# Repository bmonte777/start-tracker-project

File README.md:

# Star Tracker Project (working name)

Open-source 3-axis motorised astro head: star tracking, go-to, panoramas, time-lapse and camera control. 3D-printed prototype first, then mass production. Built to be repaired by its owner.

## Status
- Phase 1: research — done → [`docs/01-research-report.md`](docs/01-research-report.md)
- Phase 2: engineering spec — done → [`docs/02-engineering-spec.md`](docs/02-engineering-spec.md), parts list in [`hardware/bom/master-parts-list.csv`](hardware/bom/master-parts-list.csv), calculations in [`docs/calc/`](docs/calc/), decisions D1–D32 in [`docs/02-decisions-log.md`](docs/02-decisions-log.md). The spec is at revision C: size-17 reducer (D17) and 48 mm motor (D32) on azimuth. Nothing is awaiting approval

## Repository layout (planned)
| Folder | Contents |
|---|---|
| `docs/` | Research, specs, user guide, maintenance guide |
| `hardware/cad/` | 3D models (STEP for production, STL for printing) |
| `hardware/drawings/` | A4 dimensioned drawings, one part per sheet (PDF) |
| `hardware/bom/` | Bill of materials, down to the last screw, with supplier part numbers |
| `electronics/` | Schematics and PCB (KiCad) |
| `firmware/` | Motion core + application core (ASCOM Alpaca, LX200, WebSocket) |
| `app/` | Android and Windows apps |
| `website/` | Product website |

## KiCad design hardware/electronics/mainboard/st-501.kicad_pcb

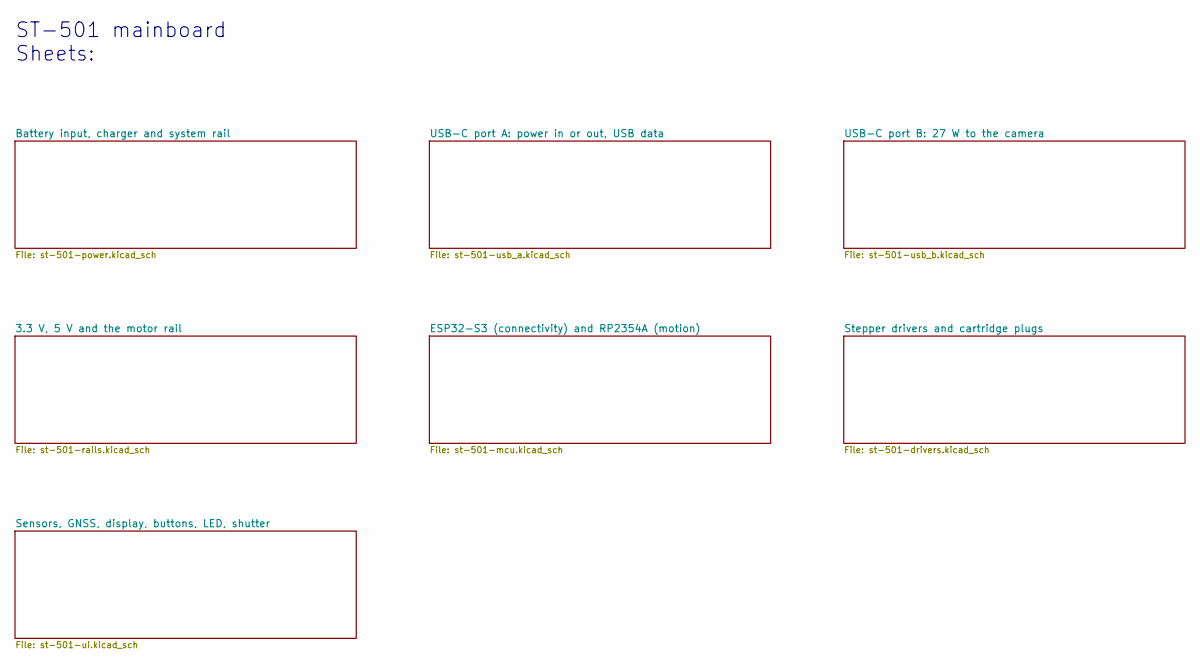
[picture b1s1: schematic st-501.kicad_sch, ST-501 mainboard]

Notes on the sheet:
ST-501 mainboard Sheets:

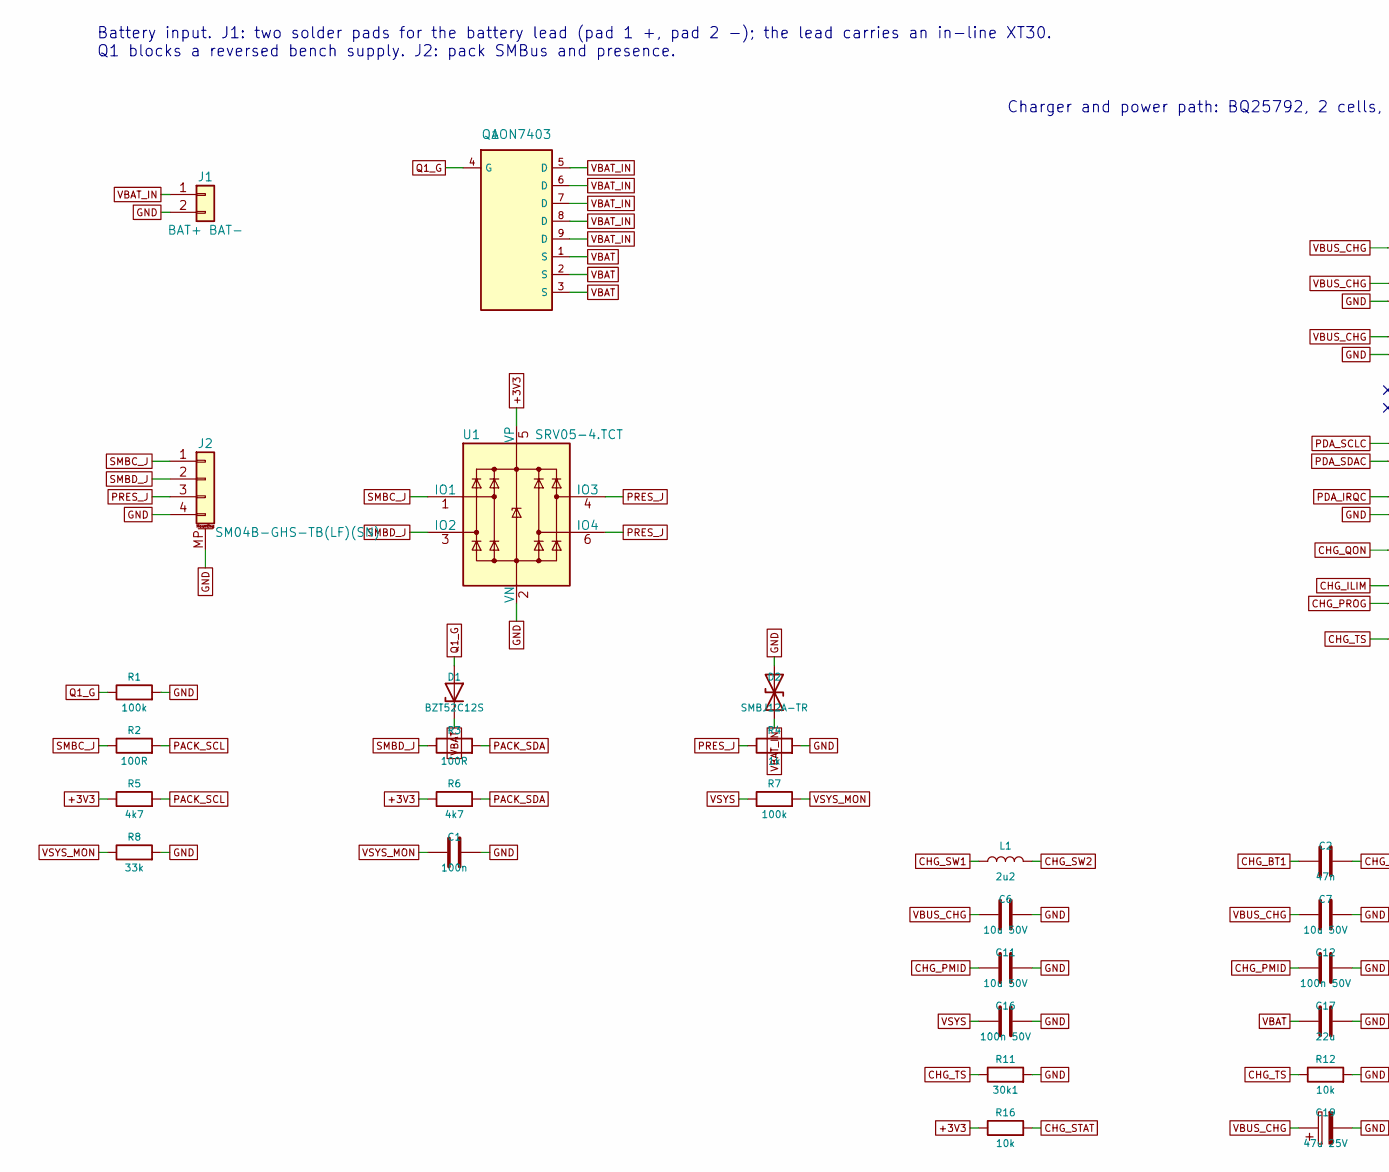
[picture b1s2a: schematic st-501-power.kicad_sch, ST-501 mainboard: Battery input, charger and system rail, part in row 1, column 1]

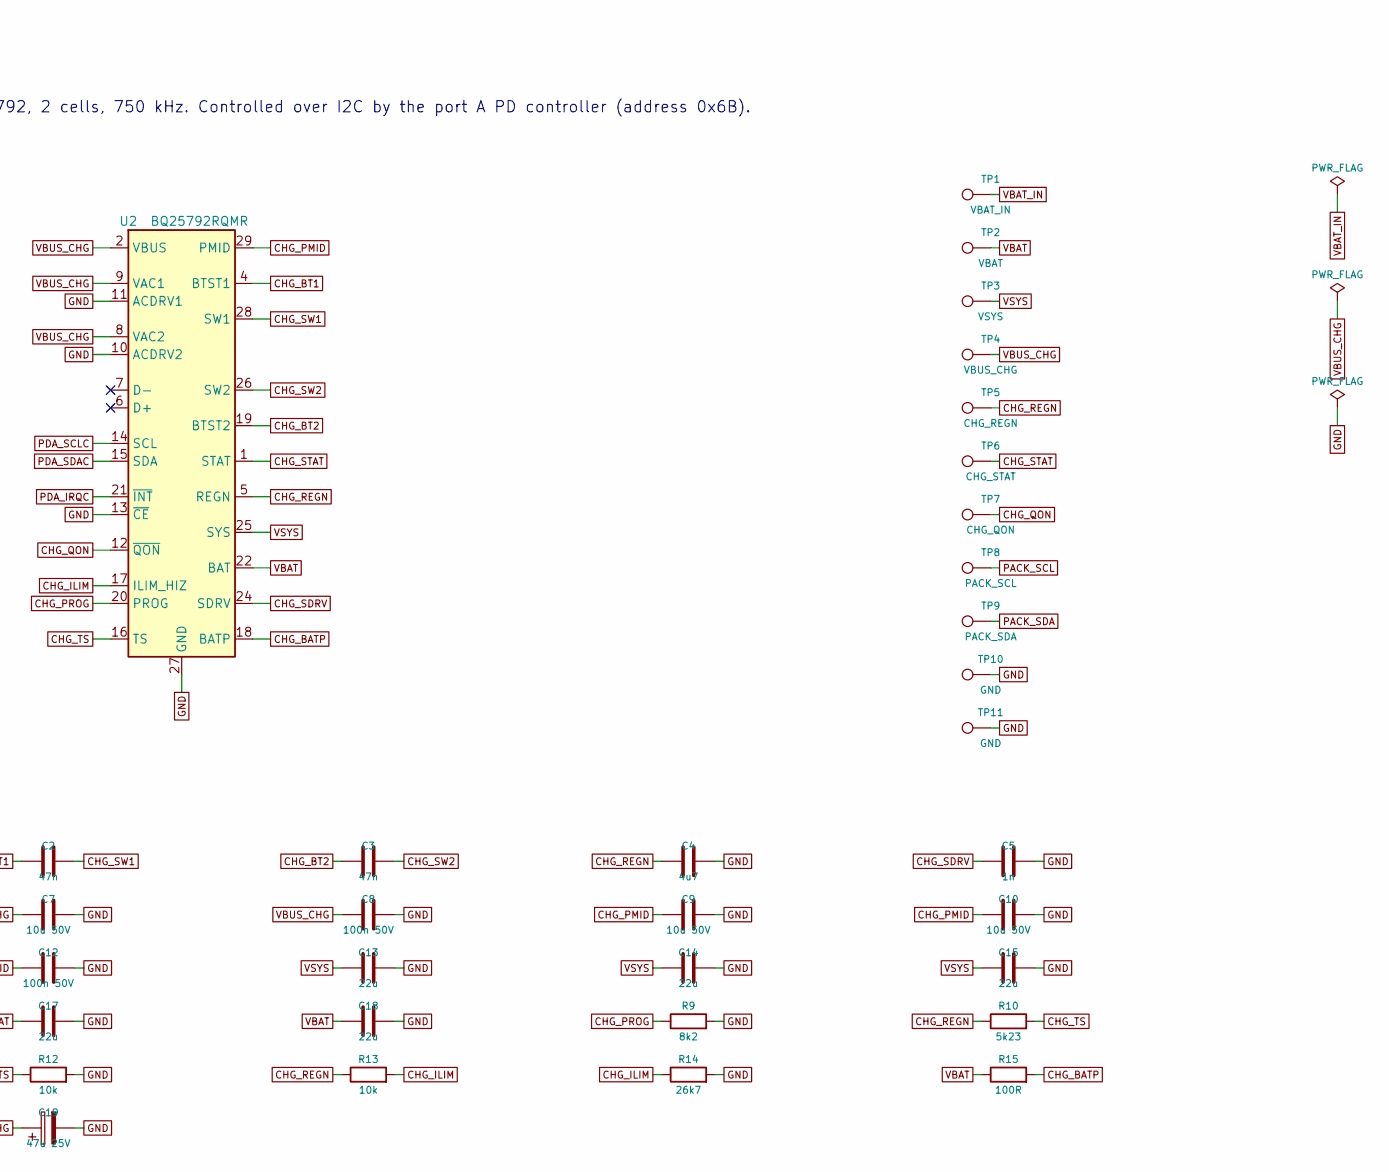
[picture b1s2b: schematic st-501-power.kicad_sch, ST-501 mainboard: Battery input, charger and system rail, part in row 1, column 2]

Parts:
C1: 100n; C_0402_1005Metric; MPN CL05B104KO5NNNC; LCSC C1525
C2, C3: 47n; C_0402_1005Metric; MPN 47 nF X7R 25 V 0402
C4: 4u7; C_0603_1608Metric; MPN CL10A475KO8NNNC; LCSC C19666
C5: 1n; C_0402_1005Metric; MPN 0402B102K500NT; LCSC C1523
C6, C7, C9, C10, C11: 10u 50V; C_1206_3216Metric; MPN CL31A106KBHNNNE; LCSC C13585
C8, C12, C16: 100n 50V; C_0402_1005Metric; MPN CL05B104KB54PNC; LCSC C307331
C13, C14, C15, C17, C18: 22u; C_0805_2012Metric; MPN CL21A226MAQNNNE; LCSC C45783
C19: 47u 25V; CP_Elec_6.3x5.8; MPN 47 uF 25 V polymer
D1: BZT52C12S; D_SOD-323; MPN BZT52C12S; LCSC C14643
D2: SMBJ12A-TR; D_SMB; MPN SMBJ12A-TR; LCSC C133677
J1: BAT+ BAT-; WirePads_1x02_P5.0mm_3.5x5mm
J2: SM04B-GHS-TB(LF)(SN); JST_GH_SM04B-GHS-TB_1x04-1MP_P1.25mm_Horizontal; MPN SM04B-GHS-TB(LF)(SN); LCSC C189895
L1: 2u2; L_Sunlord_MWSA0603S; MPN MWSC0630H2R2MT
Q1: AON7403; DFN-8-1EP_3x3mm_P0.65mm_EP1.55x2.4mm; MPN AON7403; LCSC C5310961
R1, R7: 100k; R_0402_1005Metric; MPN 0402WGF1003TCE; LCSC C25741
R2, R3, R15: 100R; R_0402_1005Metric; MPN 0402WGF1000TCE; LCSC C25076
R4: 1k; R_0402_1005Metric; MPN 0402WGF1001TCE; LCSC C11702
R5, R6: 4k7; R_0402_1005Metric; MPN 0402WGF4701TCE; LCSC C25900
R8: 33k; R_0402_1005Metric; MPN 0402WGF3302TCE; LCSC C25779
R9: 8k2; R_0402_1005Metric; MPN 0402WGF8201TCE; LCSC C25924
R10: 5k23; R_0402_1005Metric; MPN RC0402FR-075K23L; LCSC C477746
R11: 30k1; R_0402_1005Metric; MPN RC0402FR-0730K1L; LCSC C138009
R12, R13, R16: 10k; R_0402_1005Metric; MPN 0402WGF1002TCE; LCSC C25744
R14: 26k7; R_0402_1005Metric; MPN RC0402FR-0726K7L
TP1: VBAT_IN; TestPoint_Pad_D1.0mm
TP2: VBAT; TestPoint_Pad_D1.0mm
TP3: VSYS; TestPoint_Pad_D1.0mm
TP4: VBUS_CHG; TestPoint_Pad_D1.0mm
TP5: CHG_REGN; TestPoint_Pad_D1.0mm
TP6: CHG_STAT; TestPoint_Pad_D1.0mm
TP7: CHG_QON; TestPoint_Pad_D1.0mm
TP8: PACK_SCL; TestPoint_Pad_D1.0mm
TP9: PACK_SDA; TestPoint_Pad_D1.0mm
TP10, TP11: GND; TestPoint_Pad_D1.0mm
U1: SRV05-4.TCT; SOT-23-6; MPN SRV05-4.TCT; LCSC C2687126
U2: BQ25792RQMR; Texas_RQM0029A_VQFN-29_4x4mm_P0.4mm; MPN BQ25792RQMR; LCSC C2862876

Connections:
+3V3: R5.1, R6.1, R16.1, U1.5 (VP); also elsewhere on the board
CHG_BATP: R15.2, U2.18 (BATP)
CHG_BT1: C2.1, U2.4 (BTST1)
CHG_BT2: C3.1, U2.19 (BTST2)
CHG_ILIM: R13.2, R14.1, U2.17 (ILIM_HIZ)
CHG_PMID: C9.1, C10.1, C11.1, C12.1, U2.29 (PMID)
CHG_PROG: R9.1, U2.20 (PROG)
CHG_QON: TP7.1, U2.12 (~QON)
CHG_REGN: C4.1, R10.1, R13.1, TP5.1, U2.5 (REGN)
CHG_SDRV: C5.1, U2.24 (SDRV)
CHG_STAT: R16.2, TP6.1, U2.1 (STAT)
CHG_SW1: C2.2, L1.1, U2.28 (SW1)
CHG_SW2: C3.2, L1.2, U2.26 (SW2)
CHG_TS: R10.2, R11.1, R12.1, U2.16 (TS)
GND: C1.2, C4.2, C5.2, C6.2, C7.2, C8.2, C9.2, C10.2, C11.2, C12.2, C13.2, C14.2, C15.2, C16.2, C17.2, C18.2, C19.2, D2.2 (A2), J1.2, J2.4, J2.MP (MountPin), R1.2, R4.2, R8.2, R9.2, R11.2, R12.2, R14.2, TP10.1, TP11.1, U1.2 (VN), U2.10 (ACDRV2), U2.11 (ACDRV1), U2.13 (~CE), U2.27 (GND); also elsewhere on the board
PACK_SCL: R2.2, R5.2, TP8.1; also elsewhere on the board
PACK_SDA: R3.2, R6.2, TP9.1; also elsewhere on the board
PDA_IRQC: U2.21 (~INT); also elsewhere on the board
PDA_SCLC: U2.14 (SCL); also elsewhere on the board
PDA_SDAC: U2.15 (SDA); also elsewhere on the board
PRES_J: J2.3, R4.1, U1.4 (IO3), U1.6 (IO4)
Q1_G: D1.2 (A), Q1.4 (G), R1.1
SMBC_J: J2.1, R2.1, U1.1 (IO1)
SMBD_J: J2.2, R3.1, U1.3 (IO2)
VBAT: C17.1, C18.1, D1.1 (K), Q1.1 (S), Q1.2 (S), Q1.3 (S), R15.1, TP2.1, U2.22 (BAT), U2.23 (BAT)
VBAT_IN: D2.1 (A1), J1.1, Q1.5 (D), Q1.6 (D), Q1.7 (D), Q1.8 (D), Q1.9 (D), TP1.1
VBUS_CHG: C6.1, C7.1, C8.1, C19.1, TP4.1, U2.2 (VBUS), U2.3 (VBUS), U2.8 (VAC2), U2.9 (VAC1); also elsewhere on the board
VSYS: C13.1, C14.1, C15.1, C16.1, R7.1, TP3.1, U2.25 (SYS); also elsewhere on the board
VSYS_MON: C1.1, R7.2, R8.1; also elsewhere on the board

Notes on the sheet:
Battery input. J1: two solder pads for the battery lead (pad 1 +, pad 2 -); the lead carries an in-line XT30. Q1 blocks a reversed bench supply. J2: pack SMBus and presence.
Charger and power path: BQ25792, 2 cells, 750 kHz. Controlled over I2C by the port A PD controller (address 0x6B).

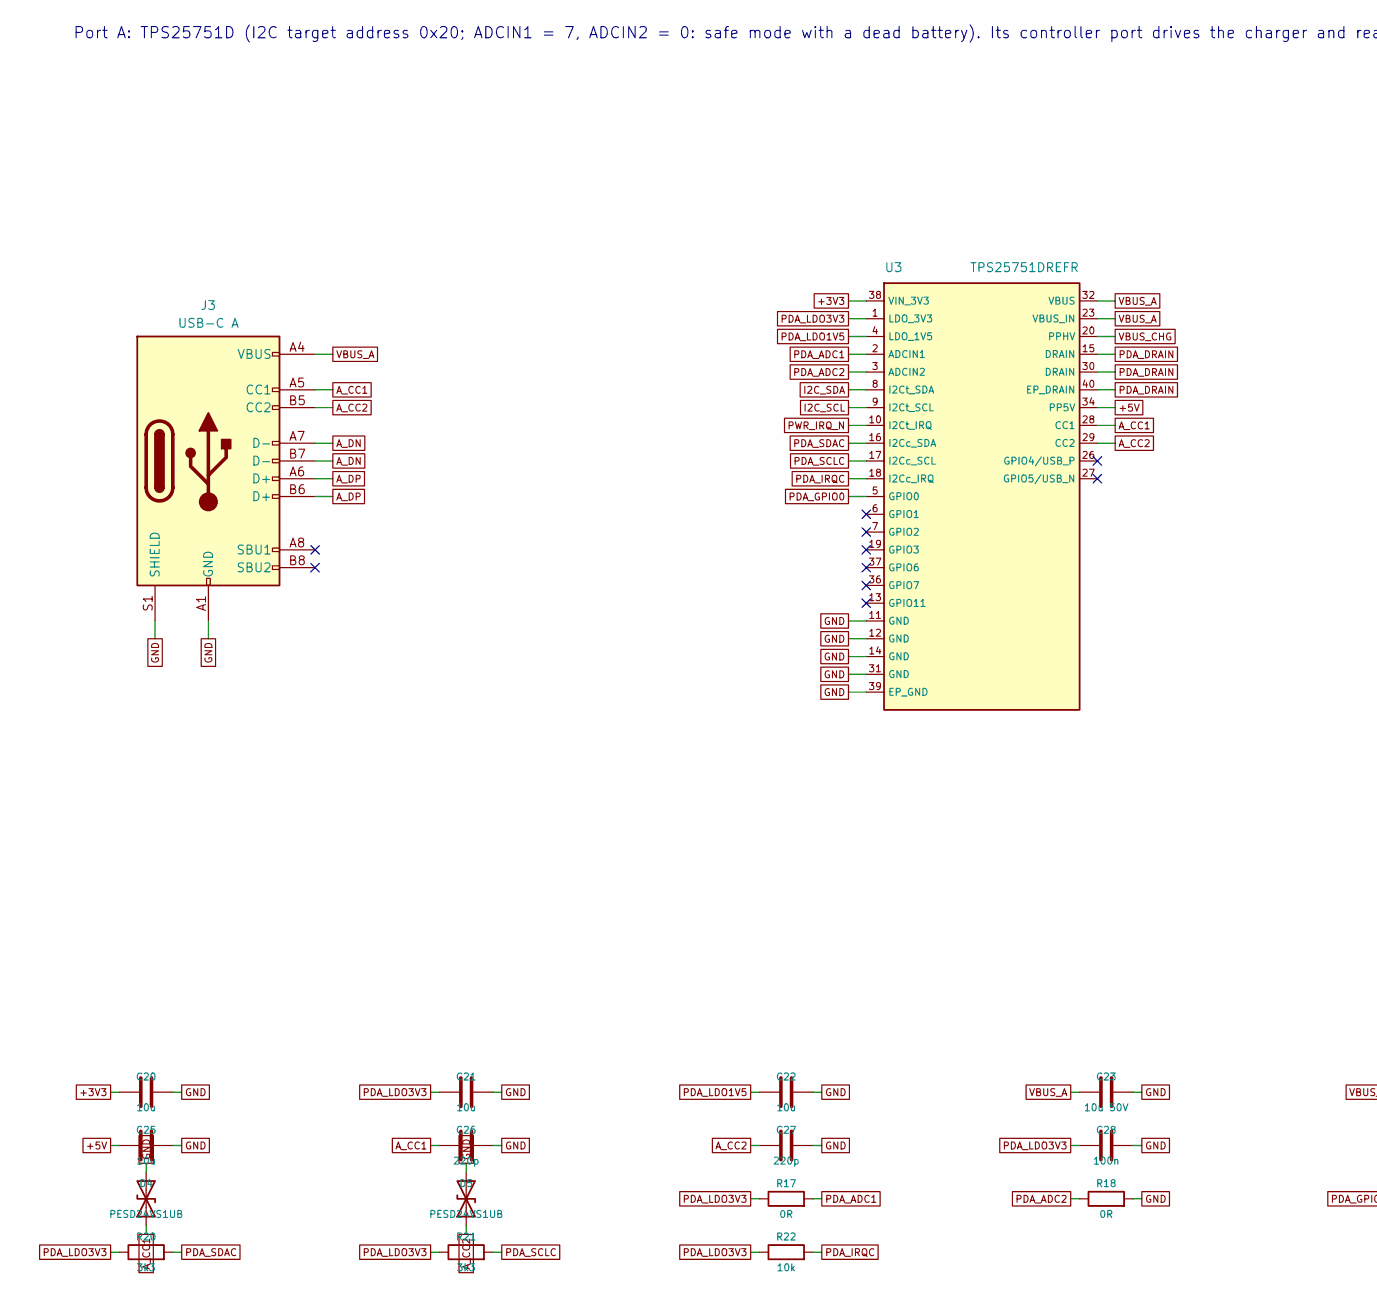
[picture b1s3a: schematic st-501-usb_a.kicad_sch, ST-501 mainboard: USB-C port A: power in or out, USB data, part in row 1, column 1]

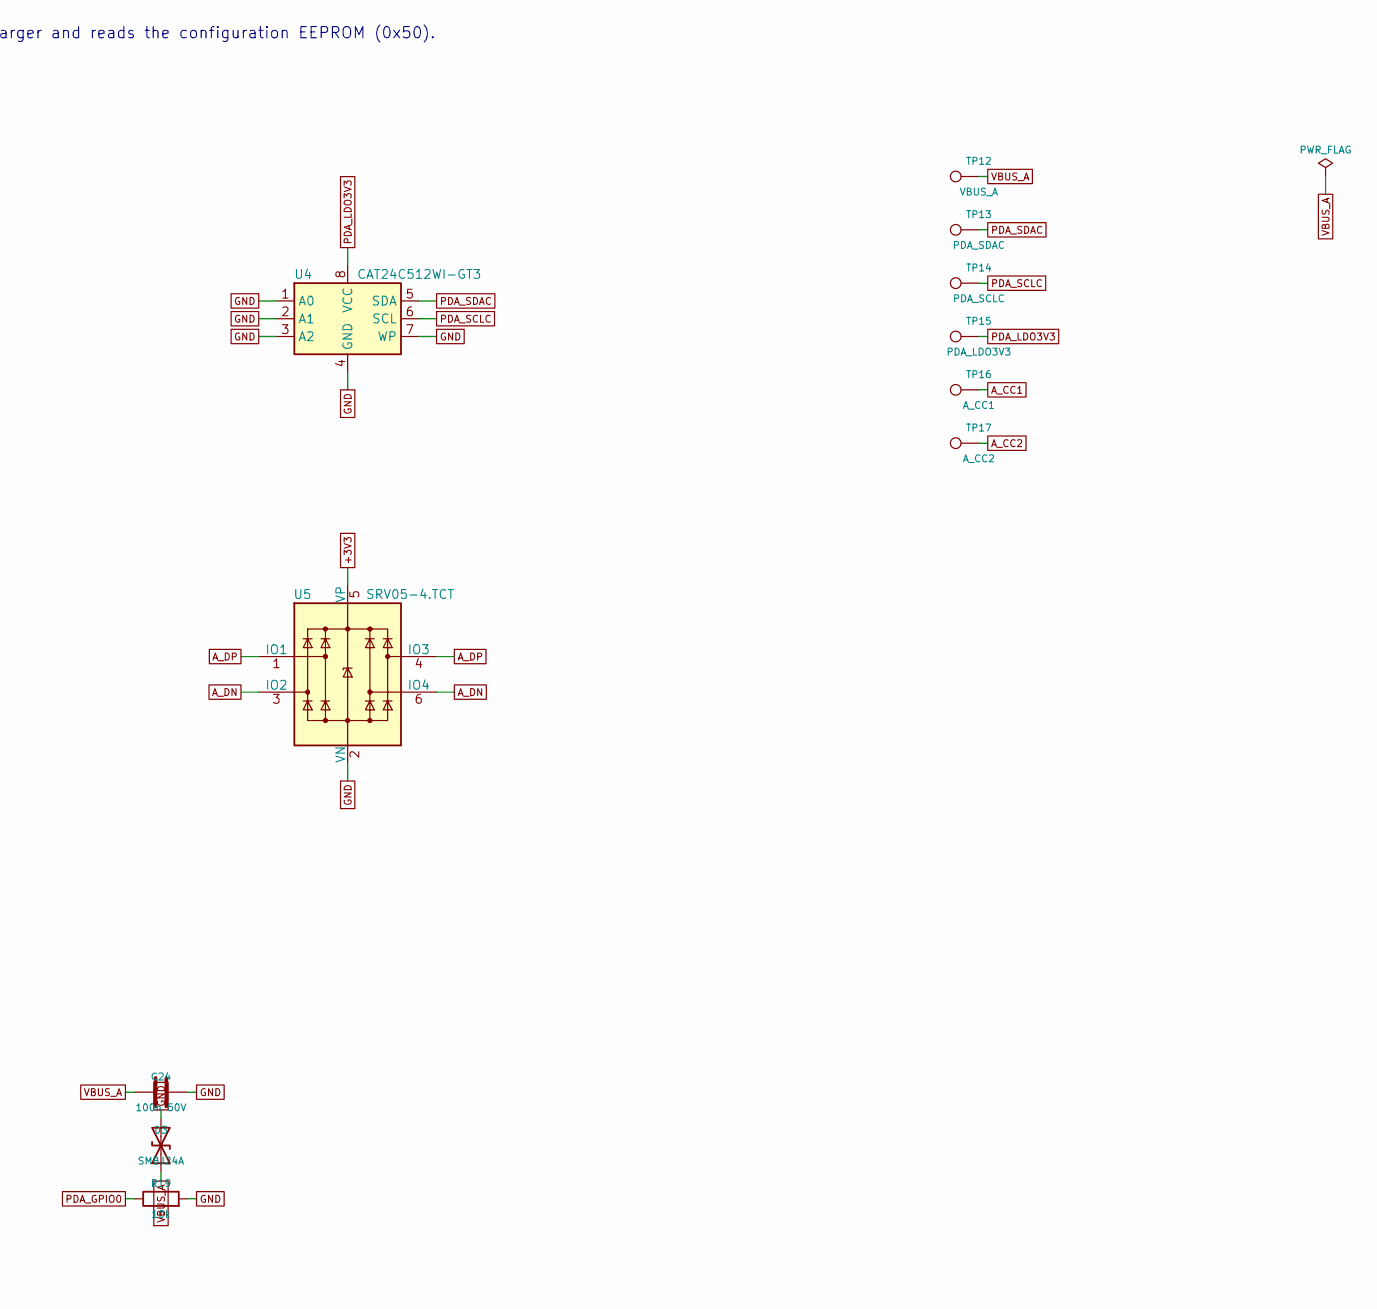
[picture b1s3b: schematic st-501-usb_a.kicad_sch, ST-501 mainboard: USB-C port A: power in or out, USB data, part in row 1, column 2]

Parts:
C20, C21, C22, C25: 10u; C_0603_1608Metric; MPN CL10A106KP8NNNC; LCSC C19702
C23: 10u 50V; C_1206_3216Metric; MPN CL31A106KBHNNNE; LCSC C13585
C24: 100n 50V; C_0402_1005Metric; MPN CL05B104KB54PNC; LCSC C307331
C26, C27: 220p; C_0402_1005Metric; MPN 0402B221K500NT; LCSC C1530
C28: 100n; C_0402_1005Metric; MPN CL05B104KO5NNNC; LCSC C1525
D3: SMBJ24A; D_SMB; MPN SMBJ24A; LCSC C353373
D4, D5: PESD24VS1UB; D_SOD-323; MPN PESD24VS1UB
J3: USB-C A; USB_C_Receptacle_G-Switch_GT-USB-7051x; MPN GT-USB-7051A; LCSC C2843970
R17, R18: 0R; R_0402_1005Metric; MPN 0402WGF0000TCE; LCSC C17168
R19, R22: 10k; R_0402_1005Metric; MPN 0402WGF1002TCE; LCSC C25744
R20, R21: 3k3; R_0402_1005Metric; MPN 0402WGF3301TCE; LCSC C25890
TP12: VBUS_A; TestPoint_Pad_D1.0mm
TP13: PDA_SDAC; TestPoint_Pad_D1.0mm
TP14: PDA_SCLC; TestPoint_Pad_D1.0mm
TP15: PDA_LDO3V3; TestPoint_Pad_D1.0mm
TP16: A_CC1; TestPoint_Pad_D1.0mm
TP17: A_CC2; TestPoint_Pad_D1.0mm
U3: TPS25751DREFR; Texas_REF0038A_WQFN-38-2EP_6x4mm_P0.4; MPN TPS25751DREFR
U4: CAT24C512WI-GT3; SOIC-8_3.9x4.9mm_P1.27mm; MPN CAT24C512WI-GT3; LCSC C79986
U5: SRV05-4.TCT; SOT-23-6; MPN SRV05-4.TCT; LCSC C2687126

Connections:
+3V3: C20.1, U3.38 (VIN_3V3), U5.5 (VP); also elsewhere on the board
+5V: C25.1, U3.34 (PP5V); also elsewhere on the board
A_CC1: C26.1, D4.1 (A1), J3.A5 (CC1), TP16.1, U3.28 (CC1)
A_CC2: C27.1, D5.1 (A1), J3.B5 (CC2), TP17.1, U3.29 (CC2)
A_DN: J3.A7 (D-), J3.B7 (D-), U5.3 (IO2), U5.6 (IO4); also elsewhere on the board
A_DP: J3.A6 (D+), J3.B6 (D+), U5.1 (IO1), U5.4 (IO3); also elsewhere on the board
GND: C20.2, C21.2, C22.2, C23.2, C24.2, C25.2, C26.2, C27.2, C28.2, D3.2 (A2), D4.2 (A2), D5.2 (A2), J3.A1 (GND), J3.A12 (GND), J3.B1 (GND), J3.B12 (GND), J3.S1 (SHIELD), R18.2, R19.2, U3.11 (GND), U3.12 (GND), U3.14 (GND), U3.31 (GND), U3.39 (EP_GND), U4.1 (A0), U4.2 (A1), U4.3 (A2), U4.4 (GND), U4.7 (WP), U5.2 (VN); also elsewhere on the board
I2C_SCL: U3.9 (I2Ct_SCL); also elsewhere on the board
I2C_SDA: U3.8 (I2Ct_SDA); also elsewhere on the board
PDA_ADC1: R17.2, U3.2 (ADCIN1)
PDA_ADC2: R18.1, U3.3 (ADCIN2)
PDA_DRAIN: U3.15 (DRAIN), U3.30 (DRAIN), U3.40 (EP_DRAIN)
PDA_GPIO0: R19.1, U3.5 (GPIO0)
PDA_IRQC: R22.2, U3.18 (I2Cc_IRQ); also elsewhere on the board
PDA_LDO1V5: C22.1, U3.4 (LDO_1V5)
PDA_LDO3V3: C21.1, C28.1, R17.1, R20.1, R21.1, R22.1, TP15.1, U3.1 (LDO_3V3), U4.8 (VCC)
PDA_SCLC: R21.2, TP14.1, U3.17 (I2Cc_SCL), U4.6 (SCL); also elsewhere on the board
PDA_SDAC: R20.2, TP13.1, U3.16 (I2Cc_SDA), U4.5 (SDA); also elsewhere on the board
PWR_IRQ_N: U3.10 (I2Ct_IRQ); also elsewhere on the board
VBUS_A: C23.1, C24.1, D3.1 (A1), J3.A4 (VBUS), J3.A9 (VBUS), J3.B4 (VBUS), J3.B9 (VBUS), TP12.1, U3.23 (VBUS_IN), U3.32 (VBUS)
VBUS_CHG: U3.20 (PPHV); also elsewhere on the board

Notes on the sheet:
Port A: TPS25751D (I2C target address 0x20; ADCIN1 = 7, ADCIN2 = 0: safe mode with a dead battery). Its controller port drives the charger and reads the configuration EEPROM (0x50).

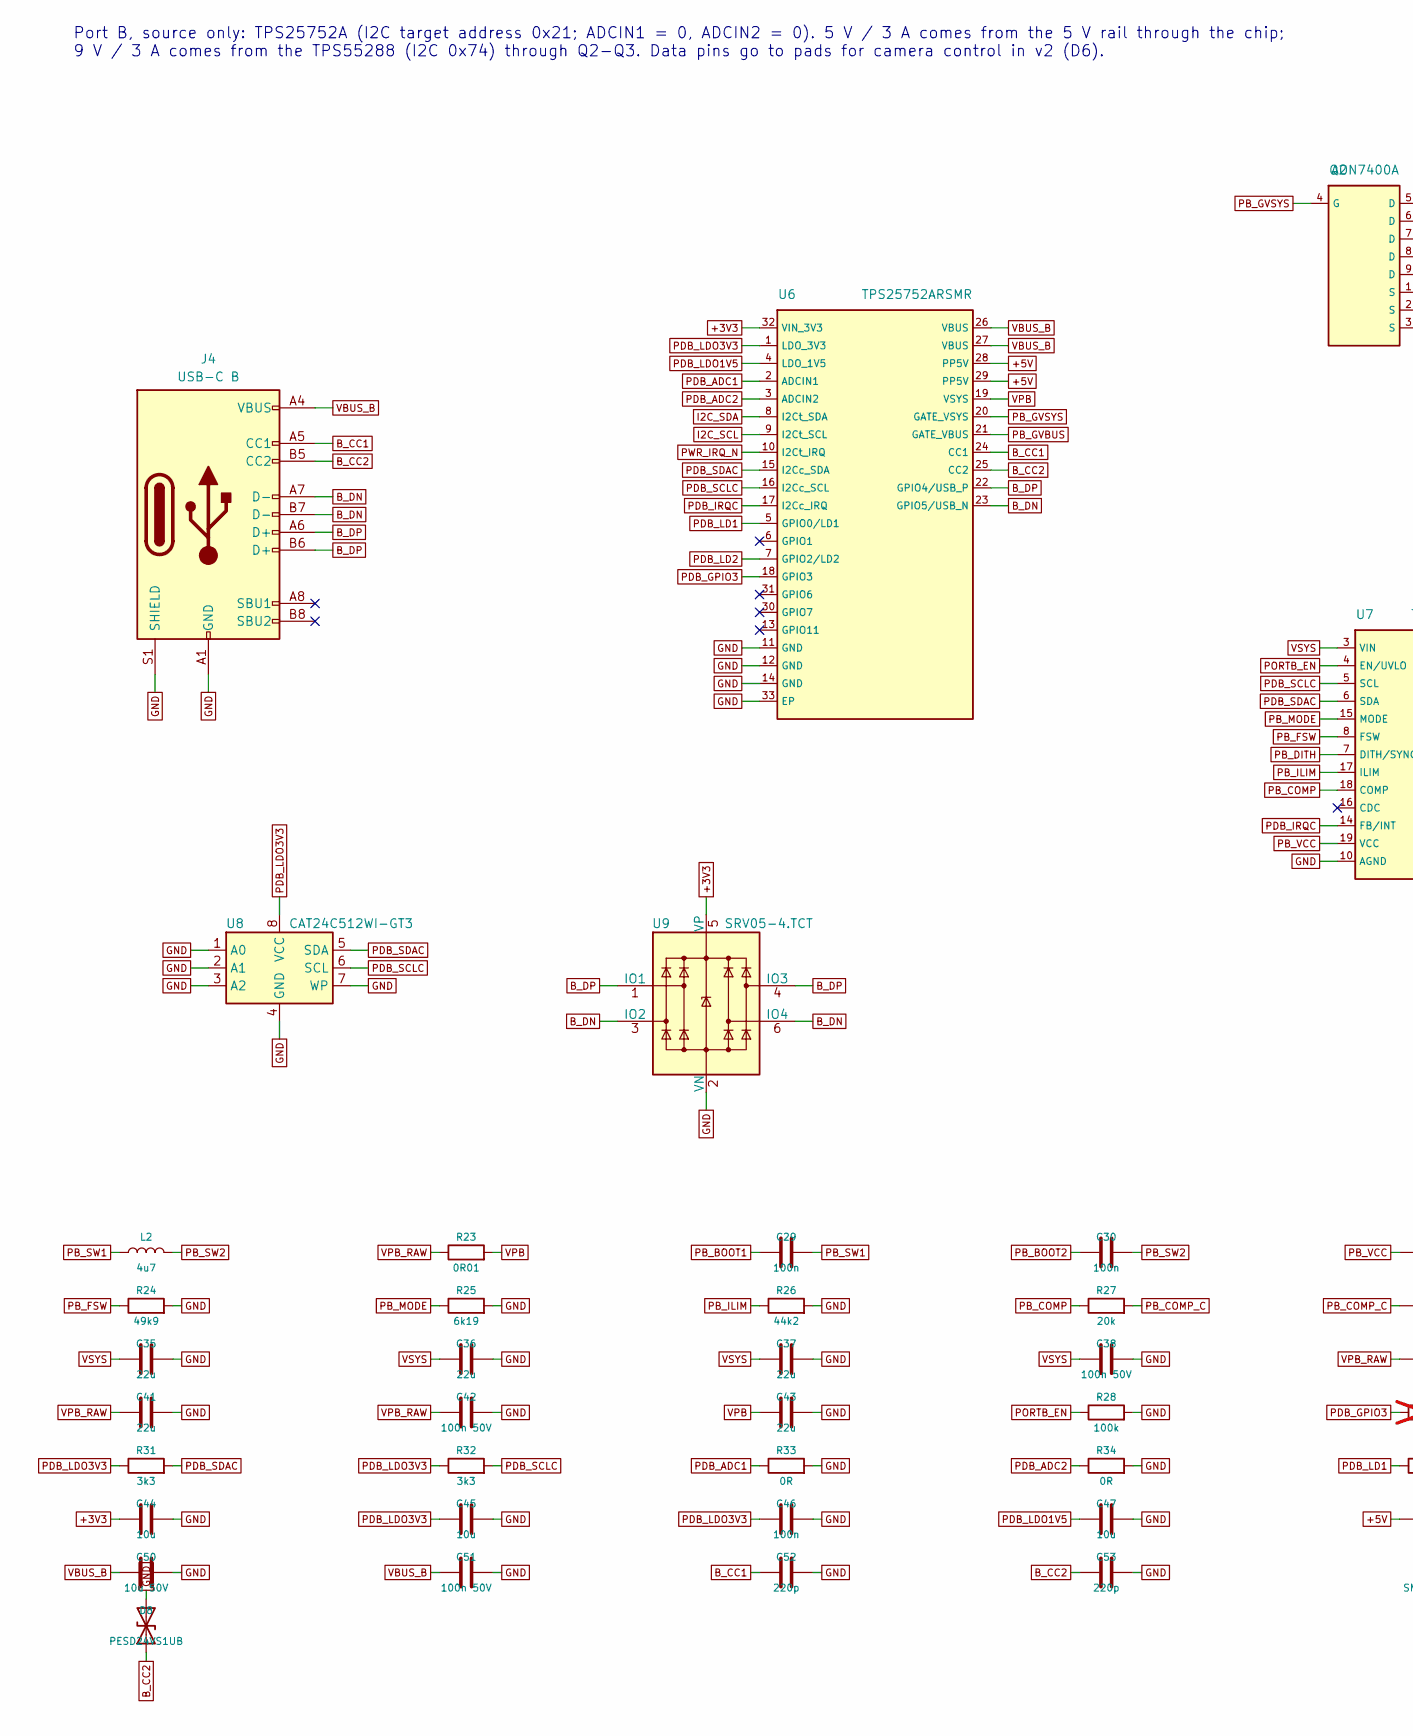
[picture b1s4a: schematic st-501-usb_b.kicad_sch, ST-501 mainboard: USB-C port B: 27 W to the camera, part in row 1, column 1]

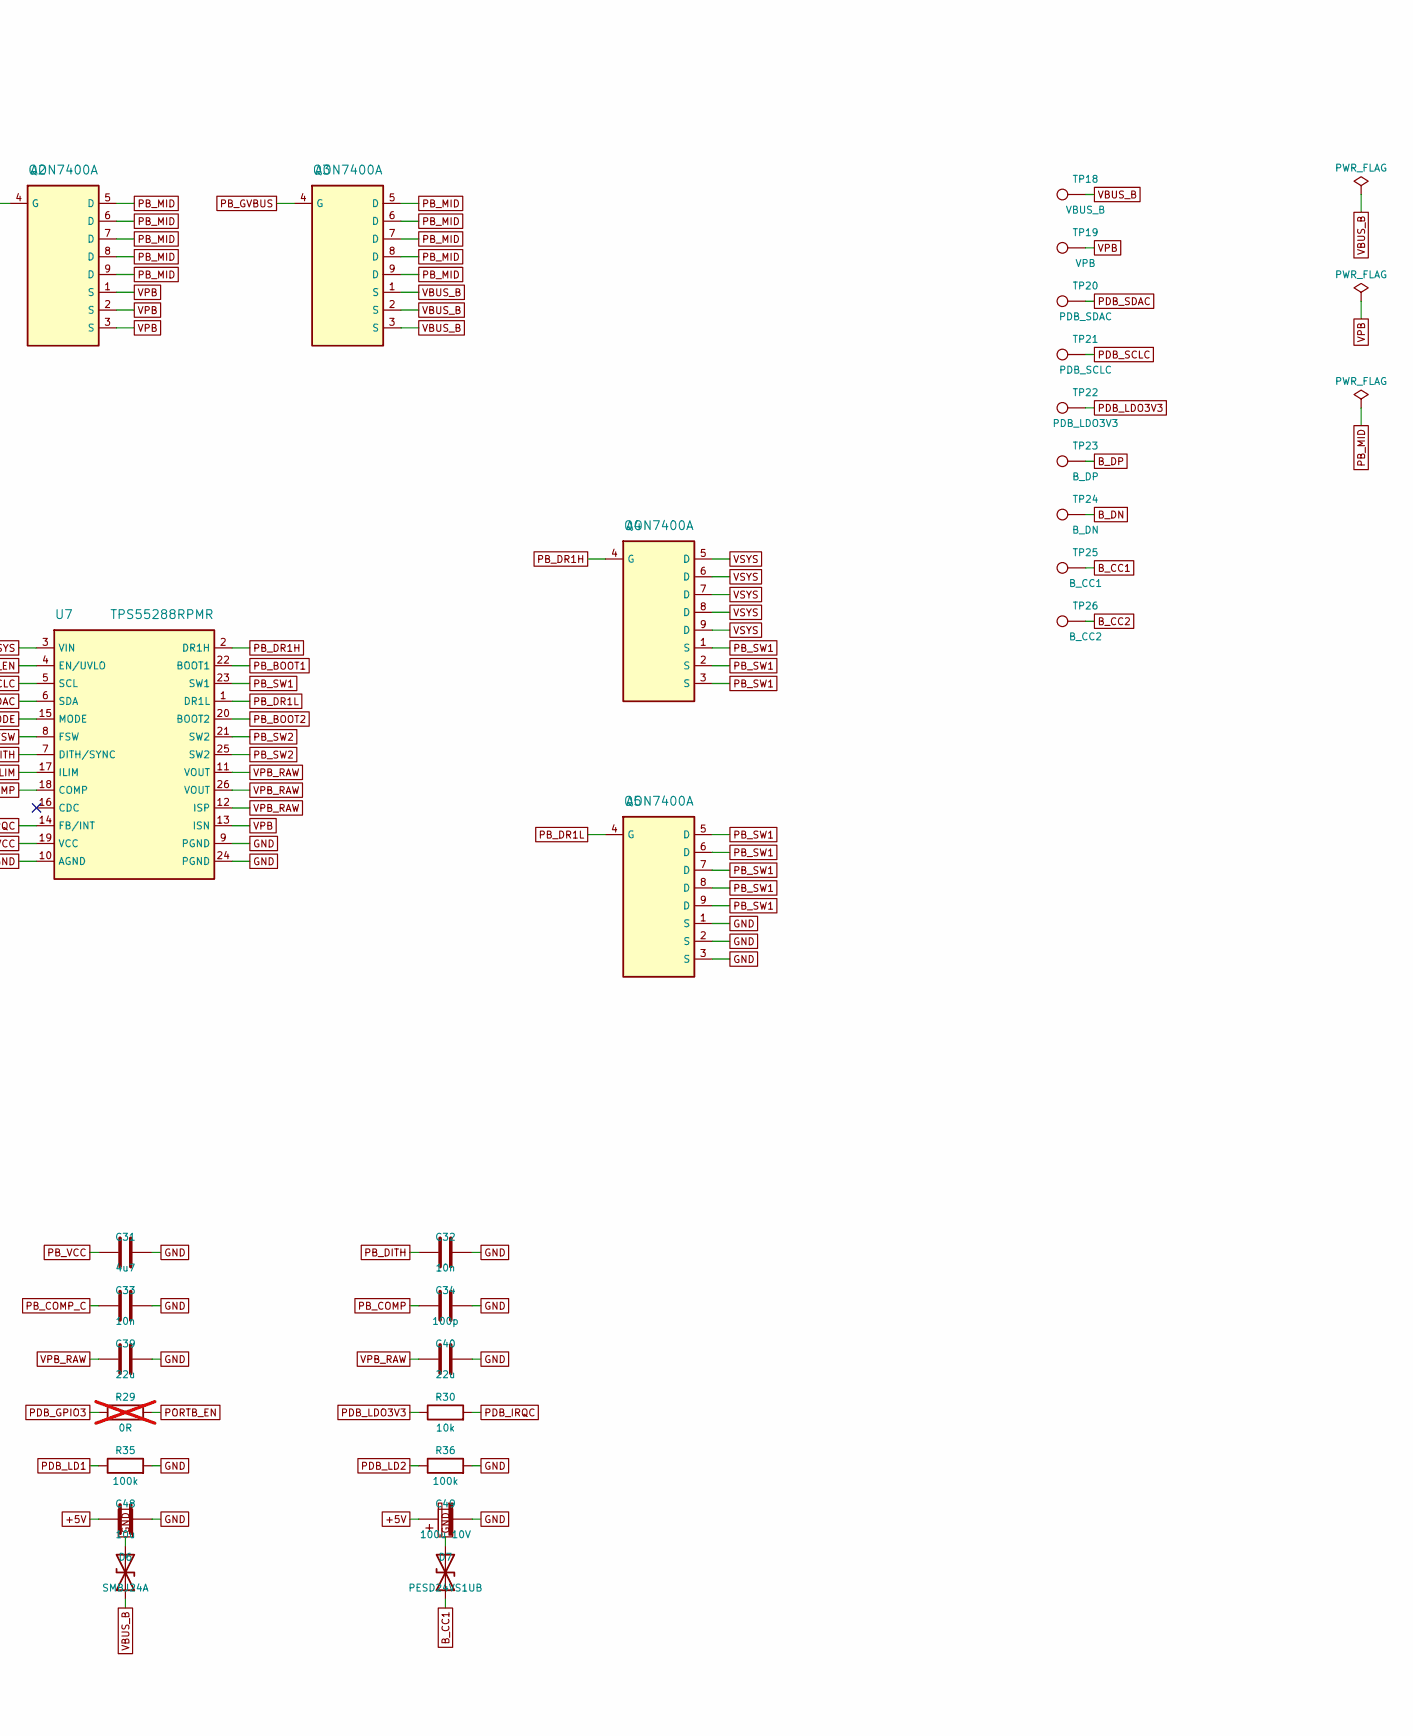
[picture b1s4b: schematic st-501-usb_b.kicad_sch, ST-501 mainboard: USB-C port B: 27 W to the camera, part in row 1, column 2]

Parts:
C29, C30, C46: 100n; C_0402_1005Metric; MPN CL05B104KO5NNNC; LCSC C1525
C31: 4u7; C_0603_1608Metric; MPN CL10A475KO8NNNC; LCSC C19666
C32, C33: 10n; C_0402_1005Metric; MPN CL05B103KB5NNNC; LCSC C15195
C34: 100p; C_0402_1005Metric; MPN CL05C101JB5NNNC; LCSC C1546
C35, C36, C37, C39, C40, C41, C43: 22u; C_0805_2012Metric; MPN CL21A226MAQNNNE; LCSC C45783
C38, C42, C51: 100n 50V; C_0402_1005Metric; MPN CL05B104KB54PNC; LCSC C307331
C44, C45, C47, C48: 10u; C_0603_1608Metric; MPN CL10A106KP8NNNC; LCSC C19702
C49: 100u 10V; CP_Elec_6.3x5.8; MPN 100 uF 10 V polymer
C50: 10u 50V; C_1206_3216Metric; MPN CL31A106KBHNNNE; LCSC C13585
C52, C53: 220p; C_0402_1005Metric; MPN 0402B221K500NT; LCSC C1530
D6: SMBJ24A; D_SMB; MPN SMBJ24A; LCSC C353373
D7, D8: PESD24VS1UB; D_SOD-323; MPN PESD24VS1UB
J4: USB-C B; USB_C_Receptacle_G-Switch_GT-USB-7051x; MPN GT-USB-7051A; LCSC C2843970
L2: 4u7; L_Sunlord_MWSA0603S; MPN MWSC0630H4R7MT; LCSC C2991788
Q2, Q3, Q4, Q5: AON7400A; DFN-8-1EP_3x3mm_P0.65mm_EP1.55x2.4mm; MPN AON7400A; LCSC C85734
R23: 0R01; R_1206_3216Metric; MPN 0.010 ohm 1 % 1 W current sense
R24: 49k9; R_0402_1005Metric; MPN 0402WGF4992TCE; LCSC C25897
R25: 6k19; R_0402_1005Metric; MPN RC0402FR-076K19L
R26: 44k2; R_0402_1005Metric; MPN RC0402FR-0744K2L
R27: 20k; R_0402_1005Metric; MPN 0402WGF2002TCE; LCSC C25765
R28, R35, R36: 100k; R_0402_1005Metric; MPN 0402WGF1003TCE; LCSC C25741
R29: 0R; R_0402_1005Metric; MPN 0402WGF0000TCE; LCSC C17168; not fitted
R30: 10k; R_0402_1005Metric; MPN 0402WGF1002TCE; LCSC C25744
R31, R32: 3k3; R_0402_1005Metric; MPN 0402WGF3301TCE; LCSC C25890
R33, R34: 0R; R_0402_1005Metric; MPN 0402WGF0000TCE; LCSC C17168
TP18: VBUS_B; TestPoint_Pad_D1.0mm
TP19: VPB; TestPoint_Pad_D1.0mm
TP20: PDB_SDAC; TestPoint_Pad_D1.0mm
TP21: PDB_SCLC; TestPoint_Pad_D1.0mm
TP22: PDB_LDO3V3; TestPoint_Pad_D1.0mm
TP23: B_DP; TestPoint_Pad_D1.0mm
TP24: B_DN; TestPoint_Pad_D1.0mm
TP25: B_CC1; TestPoint_Pad_D1.0mm
TP26: B_CC2; TestPoint_Pad_D1.0mm
U6: TPS25752ARSMR; VQFN-32-1EP_4x4mm_P0.4mm_EP2.8x2.8mm; MPN TPS25752ARSMR
U7: TPS55288RPMR; Texas_RPM0026A_VQFN-HR-26_3.5x4mm; MPN TPS55288RPMR
U8: CAT24C512WI-GT3; SOIC-8_3.9x4.9mm_P1.27mm; MPN CAT24C512WI-GT3; LCSC C79986
U9: SRV05-4.TCT; SOT-23-6; MPN SRV05-4.TCT; LCSC C2687126

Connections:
+3V3: C44.1, U6.32 (VIN_3V3), U9.5 (VP); also elsewhere on the board
+5V: C48.1, C49.1, U6.28 (PP5V), U6.29 (PP5V); also elsewhere on the board
B_CC1: C52.1, D7.1 (A1), J4.A5 (CC1), TP25.1, U6.24 (CC1)
B_CC2: C53.1, D8.1 (A1), J4.B5 (CC2), TP26.1, U6.25 (CC2)
B_DN: J4.A7 (D-), J4.B7 (D-), TP24.1, U6.23 (GPIO5/USB_N), U9.3 (IO2), U9.6 (IO4)
B_DP: J4.A6 (D+), J4.B6 (D+), TP23.1, U6.22 (GPIO4/USB_P), U9.1 (IO1), U9.4 (IO3)
GND: C31.2, C32.2, C33.2, C34.2, C35.2, C36.2, C37.2, C38.2, C39.2, C40.2, C41.2, C42.2, C43.2, C44.2, C45.2, C46.2, C47.2, C48.2, C49.2, C50.2, C51.2, C52.2, C53.2, D6.2 (A2), D7.2 (A2), D8.2 (A2), J4.A1 (GND), J4.A12 (GND), J4.B1 (GND), J4.B12 (GND), J4.S1 (SHIELD), Q5.1 (S), Q5.2 (S), Q5.3 (S), R24.2, R25.2, R26.2, R28.2, R33.2, R34.2, R35.2, R36.2, U6.11 (GND), U6.12 (GND), U6.14 (GND), U6.33 (EP), U7.9 (PGND), U7.10 (AGND), U7.24 (PGND), U8.1 (A0), U8.2 (A1), U8.3 (A2), U8.4 (GND), U8.7 (WP), U9.2 (VN); also elsewhere on the board
I2C_SCL: U6.9 (I2Ct_SCL); also elsewhere on the board
I2C_SDA: U6.8 (I2Ct_SDA); also elsewhere on the board
PB_BOOT1: C29.1, U7.22 (BOOT1)
PB_BOOT2: C30.1, U7.20 (BOOT2)
PB_COMP: C34.1, R27.1, U7.18 (COMP)
PB_COMP_C: C33.1, R27.2
PB_DITH: C32.1, U7.7 (DITH/SYNC)
PB_DR1H: Q4.4 (G), U7.2 (DR1H)
PB_DR1L: Q5.4 (G), U7.1 (DR1L)
PB_FSW: R24.1, U7.8 (FSW)
PB_GVBUS: Q3.4 (G), U6.21 (GATE_VBUS)
PB_GVSYS: Q2.4 (G), U6.20 (GATE_VSYS)
PB_ILIM: R26.1, U7.17 (ILIM)
PB_MID: Q2.5 (D), Q2.6 (D), Q2.7 (D), Q2.8 (D), Q2.9 (D), Q3.5 (D), Q3.6 (D), Q3.7 (D), Q3.8 (D), Q3.9 (D)
PB_MODE: R25.1, U7.15 (MODE)
PB_SW1: C29.2, L2.1, Q4.1 (S), Q4.2 (S), Q4.3 (S), Q5.5 (D), Q5.6 (D), Q5.7 (D), Q5.8 (D), Q5.9 (D), U7.23 (SW1)
PB_SW2: C30.2, L2.2, U7.21 (SW2), U7.25 (SW2)
PB_VCC: C31.1, U7.19 (VCC)
PDB_ADC1: R33.1, U6.2 (ADCIN1)
PDB_ADC2: R34.1, U6.3 (ADCIN2)
PDB_GPIO3: R29.1, U6.18 (GPIO3)
PDB_IRQC: R30.2, U6.17 (I2Cc_IRQ), U7.14 (FB/INT)
PDB_LD1: R35.1, U6.5 (GPIO0/LD1)
PDB_LD2: R36.1, U6.7 (GPIO2/LD2)
PDB_LDO1V5: C47.1, U6.4 (LDO_1V5)
PDB_LDO3V3: C45.1, C46.1, R30.1, R31.1, R32.1, TP22.1, U6.1 (LDO_3V3), U8.8 (VCC)
PDB_SCLC: R32.2, TP21.1, U6.16 (I2Cc_SCL), U7.5 (SCL), U8.6 (SCL)
PDB_SDAC: R31.2, TP20.1, U6.15 (I2Cc_SDA), U7.6 (SDA), U8.5 (SDA)
PORTB_EN: R28.1, R29.2, U7.4 (EN/UVLO); also elsewhere on the board
PWR_IRQ_N: U6.10 (I2Ct_IRQ); also elsewhere on the board
VBUS_B: C50.1, C51.1, D6.1 (A1), J4.A4 (VBUS), J4.A9 (VBUS), J4.B4 (VBUS), J4.B9 (VBUS), Q3.1 (S), Q3.2 (S), Q3.3 (S), TP18.1, U6.26 (VBUS), U6.27 (VBUS)
VPB: C43.1, Q2.1 (S), Q2.2 (S), Q2.3 (S), R23.2, TP19.1, U6.19 (VSYS), U7.13 (ISN)
VPB_RAW: C39.1, C40.1, C41.1, C42.1, R23.1, U7.11 (VOUT), U7.12 (ISP), U7.26 (VOUT)
VSYS: C35.1, C36.1, C37.1, C38.1, Q4.5 (D), Q4.6 (D), Q4.7 (D), Q4.8 (D), Q4.9 (D), U7.3 (VIN); also elsewhere on the board

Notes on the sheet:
Port B, source only: TPS25752A (I2C target address 0x21; ADCIN1 = 0, ADCIN2 = 0). 5 V / 3 A comes from the 5 V rail through the chip; 9 V / 3 A comes from the TPS55288 (I2C 0x74) through Q2-Q3. Data pins go to pads for camera control in v2 (D6).
